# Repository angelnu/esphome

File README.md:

# esphome
This repository contains my devices based on [ESPHome](https://esphome.io/). Each yaml in this repository represents one of my devices and can be programed following the instructions bellow.

The [devices](devices) folder contains the instructions for each device (firmware, schematics, 3D boxes, etc).

## Programming
To program/update these devices you need to:
1. create a `secrets.yaml` file. You can use `secrets_template.yaml` as base
2. start the [esphome dashboard](https://esphome.io/guides/getting_started_command_line.html#bonus-esphome-dashboard) with this git repository as config folder.
3. Connect to the dashboard 
4. First time you program your device you will need to program via a serial port. You might use a [CP2104](https://www.amazon.de/gp/product/B01CYBHM26/ref=ppx_yo_dt_b_search_asin_title?ie=UTF8&psc=1)

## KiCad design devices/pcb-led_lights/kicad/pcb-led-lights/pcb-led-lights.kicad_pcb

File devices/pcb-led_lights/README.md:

# USB Power controller

This PCB allows controlling 7 LED strip channels up to 24V and 10A per channel. I use it to control a 5x channel RGBCWWW color led strip and a 2x channel CWWW white led strip with the same device. It uses a ESP32-C6 for the improved Wifi and Bluetooth as they are placed typically in locations with bad coverage such as celings and inside walls. I programmed a custom ESPHome component for the Motor Controlled PWM as the C6 and other ESP32 variants do not include enough LEDC channels.

It also includes a push button input so it can be used (limitedly) without connection if needed. If can also be used as Bluetooth proxy (at its Flash memory size). I intend to extend it later on to use Bluetooth Low Energy switches from Shelly so that it does not depend on the Home Assistant automation being available.

I ordered [20x already assembled PCBs from PCBWay](https://www.pcbway.com/project/shareproject/Strip_LED_Controller_for_ESPHome_e175d1c1.html) as I did not want to solder and check so many myself and I installed the whole house with these. PCBWay was kind to sponsor this PCB so here is the resulting project I ordered:

I received within a month for ca 16$ each of the 20x board with most of the cost for the components. The PCBs came wrapped individually (right in the picture above) and then in groups of five (pink wrap left in the picture). It took me a couple of hours to put it in the 3D printed box (which I printed myself but can be ordered from PCBWay as well) and upload the firmware via USB C cable (no serial adapter needed).

The LED from the ESP32 will light green when connecting to Wifi and blue after the connection has been stablished.

I have also [developed an adapter PCB to connect Ikea wardrobe LEDs with the TRÅDFRI system](https://www.printables.com/model/1427264-conector-for-ikea-tradfri).

[Aisler PCB project](https://aisler.net/p/KIGTGSCT) - Alternative PCBs - not tried assembly.

<details>
<summary>KiCad PCB - schematics and assembly </summary>

- [KiCad PCB project](KiCad/pcb-led-lights/pcb-led-lights.kicad_pro)
- 
- 
- 
- 
- 
- 
  
</details>

<details>
<summary>3D Printed Box </summary>

- [3D Printed box](FreeCAD)
- [FreeCad file](FreeCAD/pcb-led-lights.FCStd)
  - fix PCB with 3x M2 screws up to 7mm long (M2X6mm work great)
  - cover slack: 0.15 mm (enough that it holds without screws)
  - all parameters of the box are in the Settings Spreadsheet that you can change with FreeCAD if you need to adjust to your case
- [3MF file - small box](FreeCAD/pcb-led-lights-Box.3mf)

</details>

<details>
<summary>Parts</summary>

- 1x [ESP32-C6 Zero](https://www.waveshare.com/wiki/ESP32-C6-Zero) - this allows for wifi 6 and reduced components to solder as programer, led and antenna are included
- 1x [AP63203WU-7 Step-Down converter](https://www.mouser.com/datasheet/2/115/DIOD_S_A0007089856_1-2542907.pdf)
- 12x [Screw Terminal blocks](https://www.amazon.de/YIXISI-Terminal-Schraubklemme-Steckverbinder-Arduino/dp/B087RN8FDZ)
- 1x [2,9 uH inductor](https://www.mouser.com/datasheet/2/3/ASPI_0628-1775153.pdf)
- 7x [SUD40N06-25L Power MOSFET](https://www.farnell.com/datasheets/69243.pdf). Can also use [STD35NF06LT4](https://www.st.com/resource/en/datasheet/std35nf06l.pdf)
- 7x 0805 SMD 47 KOhms resistor
- 2x 0805 SMD 100 nF capacitor
- 2x 0805 SMD 22 uF capacitor
- 1x 0805 SMD 10 uF capacitor
  
</details>

<details>
<summary>Firmware</summary>

- You need to modify/create your own [ESPHome.io](https://esphome.io) definition and include the [yaml in this folder](rgbww_ww_v2.yaml)
- [Example for v2](TBD)

</details>

## ToDos

- [x] v2

## Changelog

### v2

- Complete redesign using an ESP32-C6 for better WiFi and step down to handle 24V (linear regulator was getting to hot in v1)

### v1

- First version

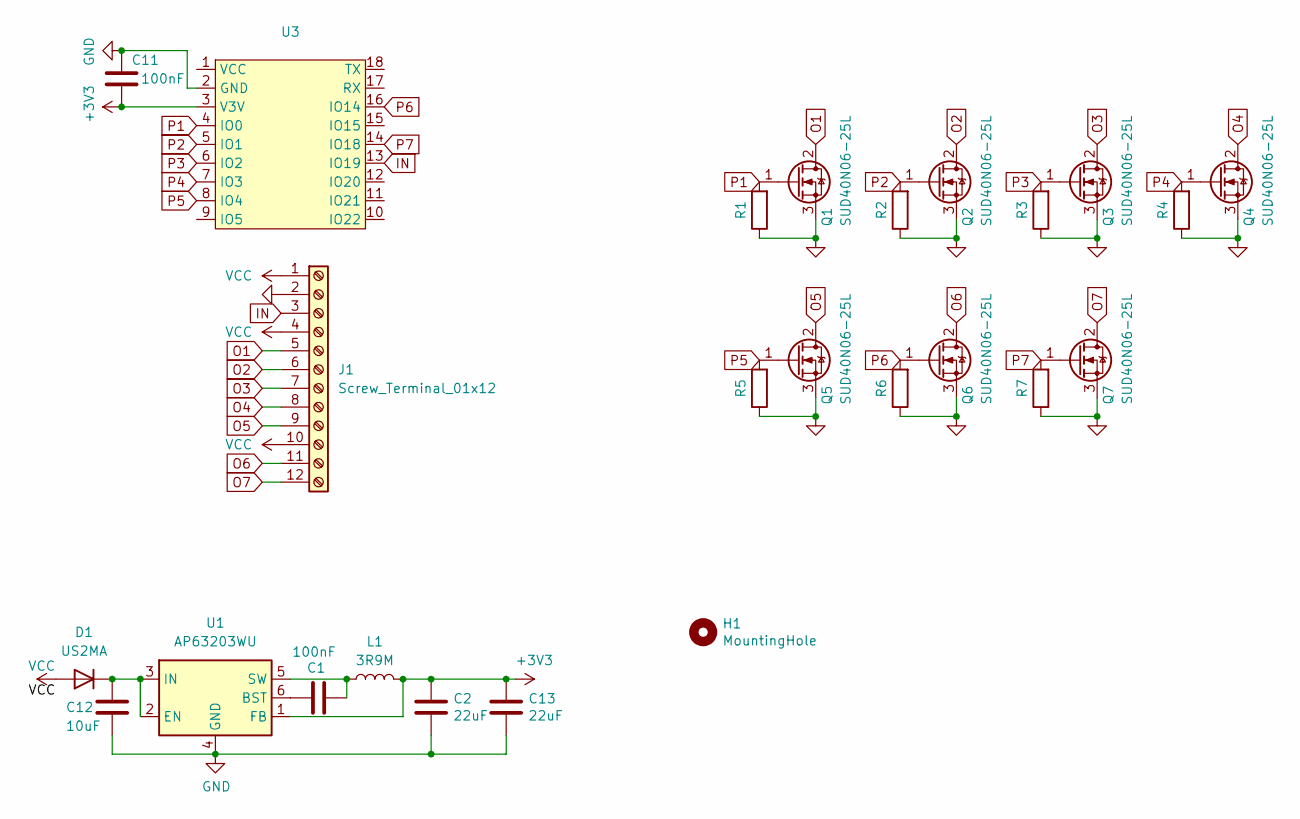
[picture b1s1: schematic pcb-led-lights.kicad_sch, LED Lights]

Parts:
C1, C11: 100nF; C_0805_2012Metric
C2, C13: 22uF; C_0805_2012Metric
C12: 10uF; C_0805_2012Metric
D1: US2MA; D_SMA
H1: MountingHole; MountingHole_2.2mm_M2
J1: Screw_Terminal_01x12; TerminalBlock_Phoenix_PT-1,5-12-5.0-H_1x12_P5.00mm_Horizont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
L1: 3R9M; L_APV_ANR6028
Q1, Q2, Q3, Q4, Q5, Q6, Q7: SUD40N06-25L; TO-252-2
R1, R2, R3, R4, R5, R6, R7: 12K; R_0805_2012Metric
U1: AP63203WU; TSOT-23-6
U3: Waveshare-ESP32-C6-Zero

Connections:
+3V3: C2.2, C11.1, C13.2, L1.2, U1.1 (FB), U3.3 (V3V)
GND: C2.1, C11.2, C12.1, C13.1, J1.2, Q1.3 (S), Q2.3 (S), Q3.3 (S), Q4.3 (S), Q5.3 (S), Q6.3 (S), Q7.3 (S), R1.1, R2.1, R3.1, R4.1, R5.1, R6.1, R7.1, U1.4 (GND), U3.2 (GND)
IN: J1.3, U3.13 (IO19)
unnamed: C12.2, D1.1 (K), U1.2 (EN), U1.3 (IN)
unnamed: C1.2, U1.6 (BST)
unnamed: C1.1, L1.1, U1.5 (SW)
O1: J1.5, Q1.2 (D)
O2: J1.6, Q2.2 (D)
O3: J1.7, Q3.2 (D)
O4: J1.8, Q4.2 (D)
O5: J1.9, Q5.2 (D)
O6: J1.11, Q6.2 (D)
O7: J1.12, Q7.2 (D)
P1: Q1.1 (G), R1.2, U3.4 (IO0)
P2: Q2.1 (G), R2.2, U3.5 (IO1)
P3: Q3.1 (G), R3.2, U3.6 (IO2)
P4: Q4.1 (G), R4.2, U3.7 (IO3)
P5: Q5.1 (G), R5.2, U3.8 (IO4)
P6: Q6.1 (G), R6.2, U3.16 (IO14)
P7: Q7.1 (G), R7.2, U3.14 (IO18)
VCC: D1.2 (A), J1.1, J1.4, J1.10

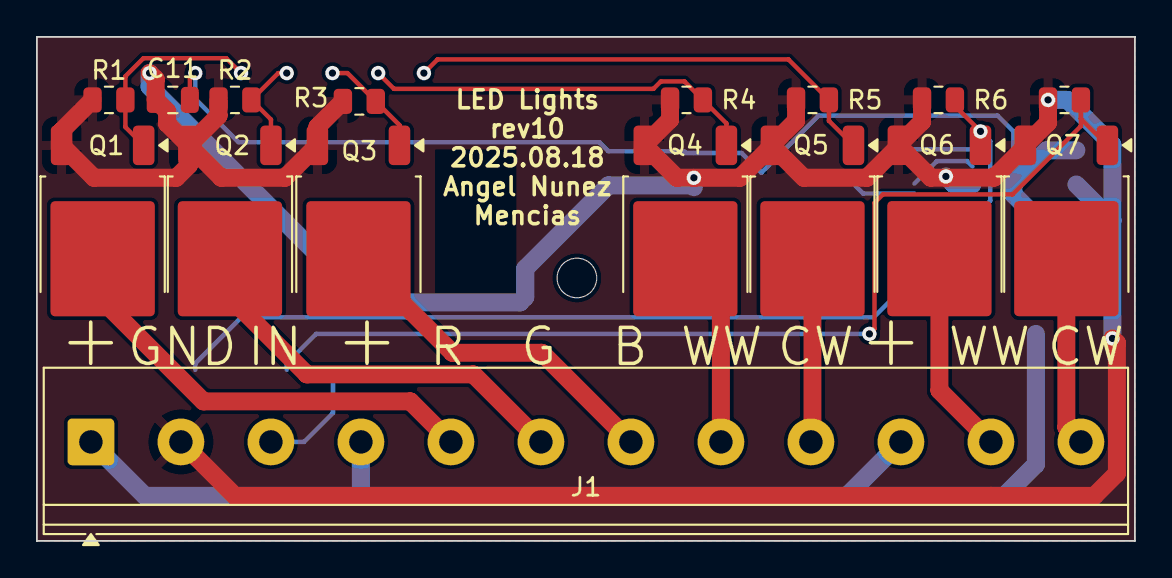
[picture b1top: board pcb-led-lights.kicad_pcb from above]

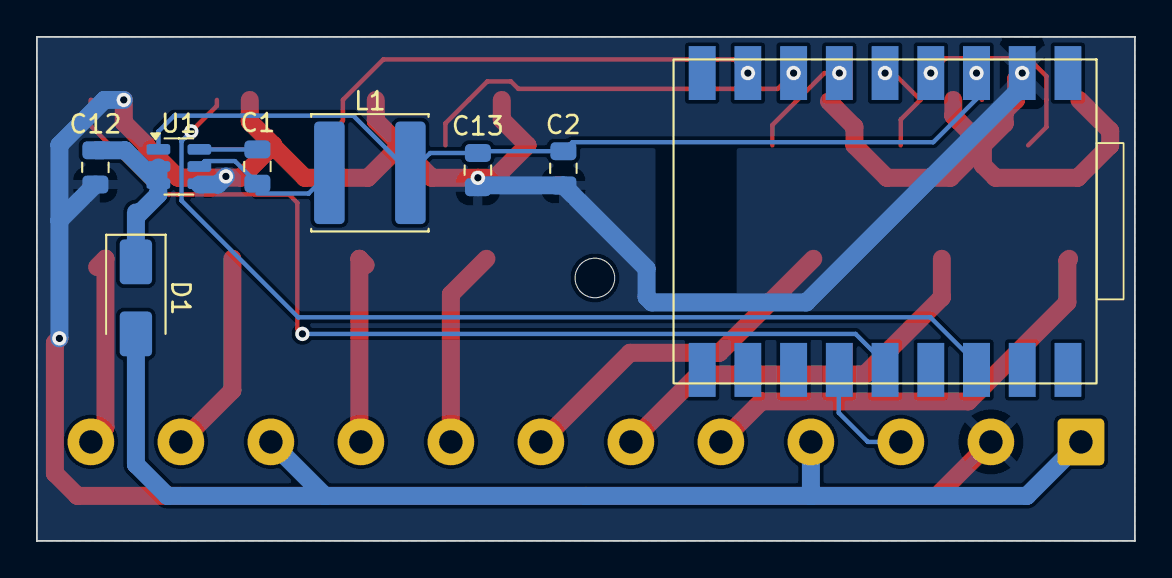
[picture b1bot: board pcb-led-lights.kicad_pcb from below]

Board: 2 copper layers, 61.0 x 28.0 mm, 25 parts (8 on the bottom side), 21 nets.

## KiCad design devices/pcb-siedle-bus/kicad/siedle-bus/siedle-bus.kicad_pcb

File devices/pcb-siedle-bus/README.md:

# Siedle In-Home bus client

This PCB allows interacting with a Sidle In-Home bus and automatically trigger actions or connect it to home automation such as [Home Assistant](https://www.home-assistant.io/). It uses [ESPHome](https://esphome.io) as base firmware. The power comes from the bus so no additional power supply is needed.

[Aisler PCB project](https://aisler.net/p/WQLXACYH)

<details>
<summary>KiCad PCB - schematics and assembly </summary>

- [KiCad PCB project](kicad/siedle-bus/siedle-bus.kicad_pro)
- 
  - [Simulation of Girator](https://www.circuitlab.com/circuit/edpfjhg6bu9k/siedle-inbus-girator/)
- 
- 
- 
- 
- 
  
</details>

<details>
<summary>3D Printed Box </summary>

- [3D Printed box](FreeCAD)
- [FreeCad file](FreeCAD/siedle-bus.FCStd)
  - fix PCB with 3x M2 screws up to 7mm long
  - use up to 3x 3mm wide screws to fix to the wall
  - cover slack: 0.15 mm (enough that it holds without screws)
  - all parameters of the box are in the Settings Spreadsheet that you can change with FreeCAD if you need to
    adjust to your case
- [3MF file - small box](FreeCAD/siedle-bus-cage.3mf)
- [3MF file - large box with placement template](FreeCAD/siedle-bus-cage_large.3mf)

</details>

<details>
<summary>Parts</summary>

- 1x [U1 - ESP32-WROOM-32 with 8MB Flash](https://www.espressif.com/sites/default/files/documentation/esp32-wroom-32_datasheet_en.pdf) / [src](https://www.chipspulse.com/product/Espressif-Systems/ESP32-WROOM-328MB.html)
- 1x [U2 - Step-down Buck Power MP1584EN Modul](https://www.ebay.de/itm/375340664282) / [alt](https://www.domoticx.net/webshop/spanningsregelaar-module-dc-dc-step-down-5-28v-naar-33v-max-3a-mp1584en/)
- 1x [2 Pin Screw Terminal blocks](https://www.amazon.de/YIXISI-Terminal-Schraubklemme-Steckverbinder-Arduino/dp/B087RN8FDZ)
- 1x [C2 - 1F 5V Supercapacitor](https://www.ebay.de/itm/126559349843) / [alt](https://www.opencircuit.nl/product/1f-supercondensator-5.5v-1-stuk)
- 2x [C3 - 220uF Elec 8x10.5 mm capacitor](https://www.ebay.de/itm/175443736870) / [alt](https://www.amazon.de/dp/B0D7GXFJ55)
- 3x [Q1, Q4, Q5 - IRLML2402 MOSFET Transistor](https://www.ebay.de/itm/114510586115) / [alt](https://www.amazon.de/dp/B08M38TJM3)
- 2x [Q2, Q3 - BC807 PNP Bipolar Transistor](https://www.ebay.de/itm/284104594986?var=585596351672) / [alt](https://www.amazon.de/dp/B08M3NZTW4)
- 1x [program_port1 - 4 pin 2.54 mm Breakaway Board Connector Header](https://www.ebay.de/itm/272575130016) / [alt](https://www.amazon.de/dp/B09BDX69VX)
- 1x [R10 - 0805 SMD 12 KOhms resistor (it can be 10K as well)](https://www.ebay.de/itm/305754891633) / [alt](https://www.amazon.de/dp/B07DK3322P)
- 5x [R1, R5, R6, 15, R16 - 0805 SMD 10 KOhms resistor](https://www.ebay.de/itm/305754891633) / [alt](https://www.amazon.de/dp/B07DK3322P)
- 1x [R7 - 0805 SMD 2 KOhms resistor](https://www.ebay.de/itm/305754891633) / [alt](https://www.amazon.de/dp/B07DK3322P)
- 2x [R8, R9 - 0805 SMD 1 KOhms resistor](https://www.ebay.de/itm/305754891633) / [alt](https://www.amazon.de/dp/B07DK3322P)
- 1x [R11 - 0805 SMD 200 Ohms resistor](https://www.ebay.de/itm/305754891633) / [alt](https://www.amazon.de/dp/B07DK3322P)
- 1x [R3 - 0805 SMD 120 Ohms resistor](https://www.ebay.de/itm/305754891633) / [alt](https://www.amazon.de/dp/B07DK3322P)
- 2x [R2, R4 - 0805 SMD 47 Ohms resistor](https://www.ebay.de/itm/305754891633) / [alt](https://www.amazon.de/dp/B07DK3322P)
- 1x [R12 - 0805 SMD 10 Ohms resistor](https://www.ebay.de/itm/305754891633) / [alt](https://www.amazon.de/dp/B07DK3322P)
- 2x [R13, R14 - 0805 SMD 0 Ohms resistor](https://www.ebay.de/itm/305754891633) / [alt](https://www.amazon.de/dp/B07DK3322P)
- 2x [C1, C11 - 0805 SMD 100 nF capacitor](https://www.ebay.de/itm/176105462805) / [alt](https://www.amazon.de/dp/B07DK4CM4W)
- 2x [D1, D2 - BYG21M 1000V 1.5A DO214AC diode](https://www.amazon.de/dp/B0DGGWWMLS)
  
</details>

<details>
<summary>Pins</summary>

- Bus connector (ETR not used). From top to bottom:
  - Tb-
  - Ta+
- Serial programming:
  - 3.3V
  - TX
  - RX
  - GND

</details>

<details>
<summary>Firmware</summary>

- You need to modify/create your own [ESPHome.io](https://esphome.io) definition and include the [yaml in this folder](v1.yaml)
- [Example for v1.0](../../interphone_small_flat.yaml)

</details>

## Bus information

The bus uses only 2 wires for communication and powering devices. A third wire is also present but not used here.

The bus provides 27V and can power client devices for up to 15mA (in the original board circuit there is a current limiter). It is very important to ensure that a high impedance is present to AC to not affect the bus communication. This is achieved in this project using a [Girator](https://en.wikipedia.org/wiki/Gyrator). The girator in this project uses a MOSFET to implement the girator and implement a virtual coil.

To prepare the bus to send a message, the bus is first shorted with 200 Ohms. This triggers the power supply of the bus to lower the current and allow the bits of the message to be sent. To send the bits a resistor of 10 ohms in parallel to the 200 Ohms is used to signal a zero while the 200 Ohms signal a 1. Each bit is 2 ms.

The PCB in this project uses a PNP Bipolar transistor to detect the bus carrier (when the voltage is dropped) and the following message bits. An NPN MOSFET is used to add the resistors to the bus.

### Message

Each message sent in the bus has 32 bits:

- 31-29: 010
- 28-23: command
- 22-18: destination
- 17-14: destination bus
- 13-12: 010 (first bit might be 1)
- 10-06: source
- 05-02: source bus
- 01-00: 00 (first bit might be 1 - broadcast?)

### References

I used all the reverse engineering from this [mikrocontroller Forum thread (german)](https://www.mikrocontroller.net/topic/308271) as base. Thanks a lot for all that contributed there.

Example of devices using this bus:

- [aib-150-01 Vendor page](https://www.siedle.de/de-de/home/service/linked-pages/produktkatalog/tuersprechanlagen-innen/siedle-basic/aib-150-01/)

### ToDos

- [x] switch to esp-idf framework

## Changelog

### v1

- First version

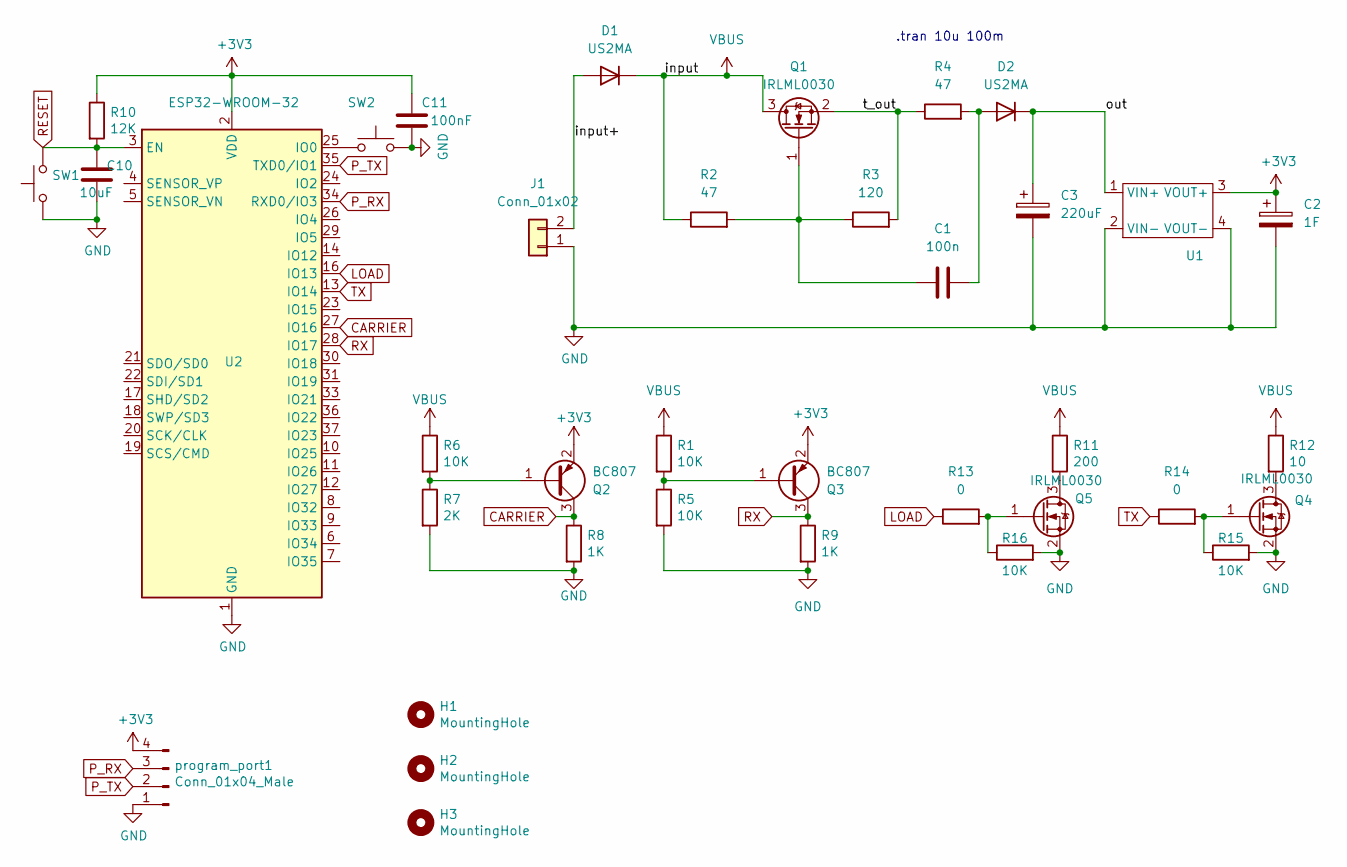
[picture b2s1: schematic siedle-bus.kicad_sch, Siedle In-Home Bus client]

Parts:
C1: 100n; C_0805_2012Metric
C2: 1F; CP_Radial_Tantal_D20.5mm_P5.00mm
C3: 220uF; CP_Elec_8x10.5
C10: 10uF; C_0805_2012Metric
C11: 100nF; C_0805_2012Metric
D1, D2: US2MA; D_SMA
H1, H2, H3: MountingHole; MountingHole_2.2mm_M2
J1: Conn_01x02; PhoenixContact_MCV_1,5_2-G-5.08_1x02_P5.08mm_Vertical
Q1, Q4, Q5: IRLML0030; SOT-23
Q2, Q3: BC807; SOT-23
R1, R5, R6, R15, R16: 10K; R_0805_2012Metric
R2, R4: 47; R_0805_2012Metric
R3: 120; R_0805_2012Metric
R7: 2K; R_0805_2012Metric
R8, R9: 1K; R_0805_2012Metric
R10: 12K; R_0805_2012Metric
R11: 200; R_0805_2012Metric
R12: 10; R_0805_2012Metric
R13, R14: 0; R_0805_2012Metric
SW1: RESET; SW_SPST_PTS810
SW2: BOOT; SW_SPST_PTS810
U1: SRT_MPT1584EN_Module
U2: ESP32-WROOM-32
program_port1: Conn_01x04_Male; PinHeader_1x04_P2.54mm_Vertical

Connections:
+3V3: C2.1, C11.2, Q2.2 (E), Q3.2 (E), R10.1, U1.3 (VOUT+), U2.2 (VDD), program_port1.4
/input+: D1.2 (A), J1.2
/out: C3.1, D2.1 (K), U1.1 (VIN+)
/t_out: Q1.2 (S), R3.2, R4.1
CARRIER: Q2.3 (C), R8.1, U2.27 (IO16)
GND: C2.2, C3.2, C10.1, C11.1, J1.1, Q4.2 (S), Q5.2 (S), R5.2, R7.2, R8.2, R9.2, R15.2, R16.2, SW1.1, SW2.2, U1.2 (VIN-), U1.4 (VOUT-), U2.1 (GND), U2.15 (GND), U2.38 (GND), U2.39 (GND), program_port1.1
LOAD: R13.1, U2.16 (IO13)
unnamed: C1.2, D2.2 (A), R4.2
unnamed: C1.1, Q1.1 (G), R2.2, R3.1
unnamed: Q2.1 (B), R6.2, R7.1
unnamed: Q3.1 (B), R1.2, R5.1
unnamed: Q4.3 (D), R12.2
unnamed: Q4.1 (G), R14.2, R15.1
unnamed: Q5.3 (D), R11.2
unnamed: Q5.1 (G), R13.2, R16.1
unnamed: SW2.1, U2.25 (IO0)
P_RX: U2.34 (RXD0/IO3), program_port1.3
P_TX: U2.35 (TXD0/IO1), program_port1.2
RESET: C10.2, R10.2, SW1.2, U2.3 (EN)
RX: Q3.3 (C), R9.1, U2.28 (IO17)
TX: R14.1, U2.13 (IO14)
VBUS: D1.1 (K), Q1.3 (D), R1.1, R2.1, R6.1, R11.1, R12.1

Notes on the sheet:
.tran 10u 100m

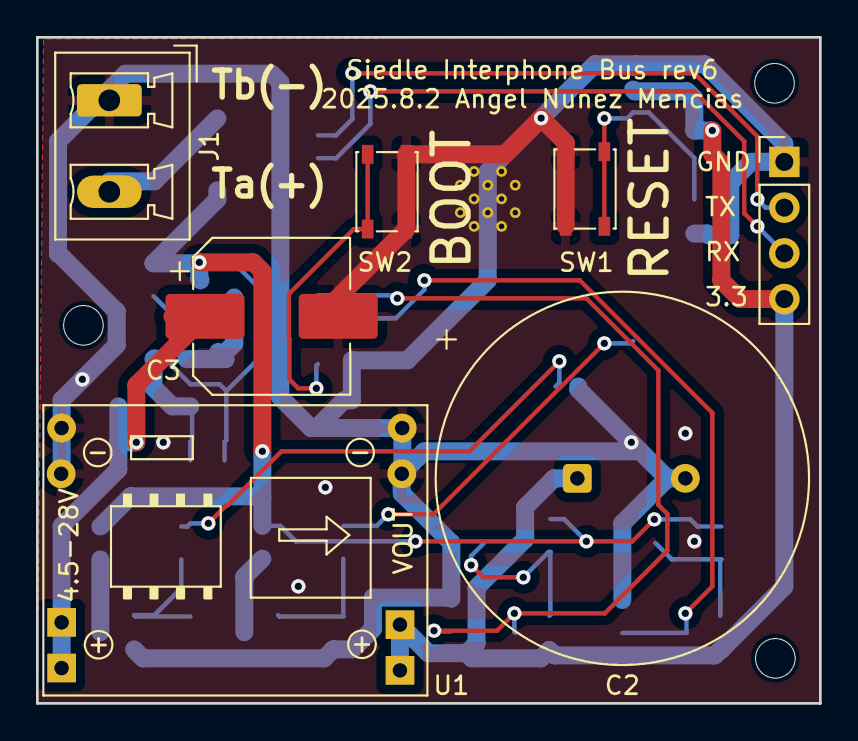
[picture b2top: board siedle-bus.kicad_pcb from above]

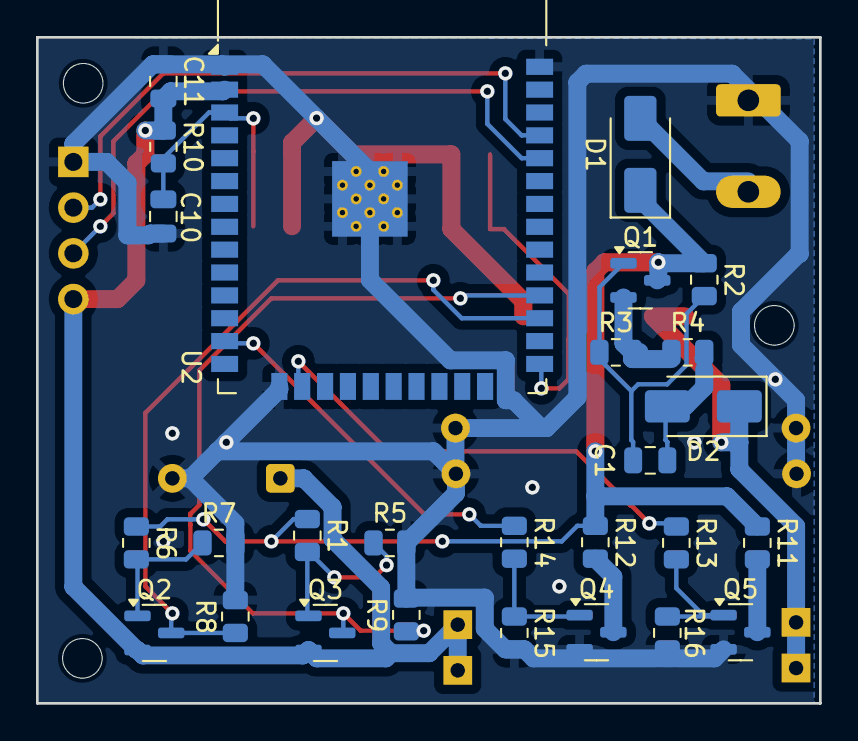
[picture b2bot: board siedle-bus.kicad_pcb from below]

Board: 2 copper layers, 43.5 x 37.0 mm, 37 parts (27 on the bottom side), 22 nets.

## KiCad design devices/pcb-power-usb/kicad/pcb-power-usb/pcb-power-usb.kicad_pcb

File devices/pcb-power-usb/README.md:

# USB Power controller

This PCB allows providing 5 V for up to 8 USB devices. Each of them can be disabled via esphome. Each USB has an LED to indicate if power is provided.

- 

- [Aisler PCB project](https://aisler.net/p/BQLUSDIS)
- [KiCad PCB](kicad/pcb-power-usb/pcb-power-usb.kicad_pro)
  - 
  - 
  - 
- [3D Printed cage](cage):
  - [Fusion 360 online view](https://a360.co/3qWptNk)
  - [Fusion 360 archive](cage/pcb-power-usb.f3z)

- Parts:
  - 1x [ESP32-WROOM-32](https://www.espressif.com/sites/default/files/documentation/esp32-wroom-32_datasheet_en.pdf)
  - 1x [AMS1117 - 3,3v 1A regulator in SOT-223 format](http://www.advanced-monolithic.com/pdf/ds1117.pdf)
  - 8x [IRLML0030 - 5A N-MOSFET](https://www.infineon.com/dgdl/Infineon-IRLML0030-DataSheet-v01_01-EN.pdf?fileId=5546d462533600a401535664773825df)
  - 8x [USB_A_Stewart_SS-52100-001_Horizontal](https://www.digikey.de/en/products/detail/stewart-connector/SS-52100-001/7902377)
  - 8x 0805 LEDs
  - 8x 0805 LED resistors (depends on selected LED)
  - 1x 10 KOhm resistor (reset)
  - 9x 0805 10 uF capacitor
  - 1x DC 5.5 x 2.1 mm barrel connector
    - Bought from [Amazon](https://www.amazon.de/gp/product/B093FTFZ8Q)
- PINs:
  - Header top left - external temperature sensors. From top to bottom:
    - VCC
    - Data
    - GND
- Firmware: [esphome](esphome.io)
  - You need to modify/create your own esphome definition and include the yaml in this folder matching your PCB
  - [Example for v1.0](../../s13-legos-shelves.yaml)

# Changelog

## v1.0
  - First version
  - BUGS:
    - None so far

## v2.0
    - use outputs instead of switches so optionally lights can be used

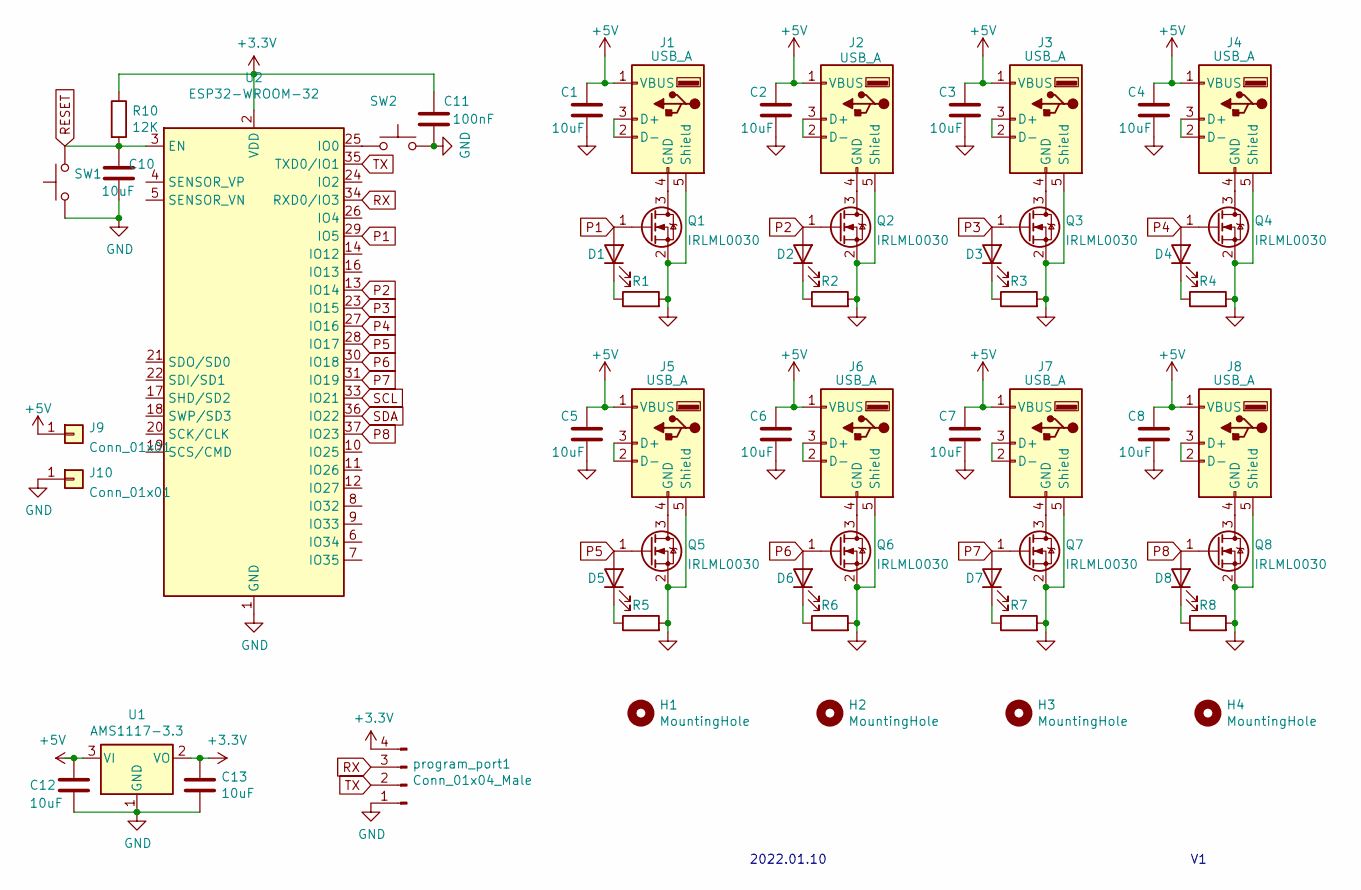
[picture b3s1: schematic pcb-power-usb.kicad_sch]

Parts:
C1, C2, C3, C4, C5, C6, C7, C8, C10, C12, C13: 10uF; C_0805_2012Metric
C11: 100nF; C_0805_2012Metric
D1, D2, D3, D4, D5, D6, D7, D8: LED; LED_0805_2012Metric_Pad1.15x1.40mm_HandSolder
H1, H2, H3, H4: MountingHole; MountingHole_2.2mm_M2
J1, J2, J3, J4, J5, J6, J7, J8: USB_A; USB_A_Stewart_SS-52100-001_Horizontal
J9, J10: Conn_01x01; SolderWire-1sqmm_1x01_D1.4mm_OD2.7mm
Q1, Q2, Q3, Q4, Q5, Q6, Q7, Q8: IRLML0030; SOT-23
R1, R2, R3, R4, R5, R6, R7, R8: R; R_0805_2012Metric
R10: 12K; R_0805_2012Metric
SW1, SW2: SW_Push; SW_SPST_PTS810
U1: AMS1117-3.3; SOT-223-3_TabPin2
U2: ESP32-WROOM-32
program_port1: Conn_01x04_Male; PinHeader_1x04_P2.54mm_Vertical

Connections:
+3V3: C11.2, C13.2, R10.1, U1.2 (VO), U2.2 (VDD), program_port1.4
+5V: C1.2, C2.2, C3.2, C4.2, C5.2, C6.2, C7.2, C8.2, C12.2, J1.1 (VBUS), J2.1 (VBUS), J3.1 (VBUS), J4.1 (VBUS), J5.1 (VBUS), J6.1 (VBUS), J7.1 (VBUS), J8.1 (VBUS), J9.1, U1.3 (VI)
GND: C1.1, C2.1, C3.1, C4.1, C5.1, C6.1, C7.1, C8.1, C10.1, C11.1, C12.1, C13.1, J1.5 (Shield), J2.5 (Shield), J3.5 (Shield), J4.5 (Shield), J5.5 (Shield), J6.5 (Shield), J7.5 (Shield), J8.5 (Shield), J10.1, Q1.2 (S), Q2.2 (S), Q3.2 (S), Q4.2 (S), Q5.2 (S), Q6.2 (S), Q7.2 (S), Q8.2 (S), R1.2, R2.2, R3.2, R4.2, R5.2, R6.2, R7.2, R8.2, SW1.1, SW2.2, U1.1 (GND), U2.1 (GND), U2.15 (GND), U2.38 (GND), U2.39 (GND), program_port1.1
unnamed: D1.1 (K), R1.1
unnamed: D2.1 (K), R2.1
unnamed: D3.1 (K), R3.1
unnamed: D4.1 (K), R4.1
unnamed: D5.1 (K), R5.1
unnamed: D6.1 (K), R6.1
unnamed: D7.1 (K), R7.1
unnamed: D8.1 (K), R8.1
unnamed: J1.2 (D-), J1.3 (D+)
unnamed: J1.4 (GND), Q1.3 (D)
unnamed: J2.2 (D-), J2.3 (D+)
unnamed: J2.4 (GND), Q2.3 (D)
unnamed: J3.2 (D-), J3.3 (D+)
unnamed: J3.4 (GND), Q3.3 (D)
unnamed: J4.2 (D-), J4.3 (D+)
unnamed: J4.4 (GND), Q4.3 (D)
unnamed: J5.2 (D-), J5.3 (D+)
unnamed: J5.4 (GND), Q5.3 (D)
unnamed: J6.2 (D-), J6.3 (D+)
unnamed: J6.4 (GND), Q6.3 (D)
unnamed: J7.2 (D-), J7.3 (D+)
unnamed: J7.4 (GND), Q7.3 (D)
unnamed: J8.2 (D-), J8.3 (D+)
unnamed: J8.4 (GND), Q8.3 (D)
unnamed: SW2.1, U2.25 (IO0)
P1: D1.2 (A), Q1.1 (G), U2.29 (IO5)
P2: D2.2 (A), Q2.1 (G), U2.13 (IO14)
P3: D3.2 (A), Q3.1 (G), U2.23 (IO15)
P4: D4.2 (A), Q4.1 (G), U2.27 (IO16)
P5: D5.2 (A), Q5.1 (G), U2.28 (IO17)
P6: D6.2 (A), Q6.1 (G), U2.30 (IO18)
P7: D7.2 (A), Q7.1 (G), U2.31 (IO19)
P8: D8.2 (A), Q8.1 (G), U2.37 (IO23)
RESET: C10.2, R10.2, SW1.2, U2.3 (EN)
RX: U2.34 (RXD0/IO3), program_port1.3
SCL: U2.33 (IO21)
SDA: U2.36 (IO22)
TX: U2.35 (TXD0/IO1), program_port1.2

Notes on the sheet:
2022.01.10

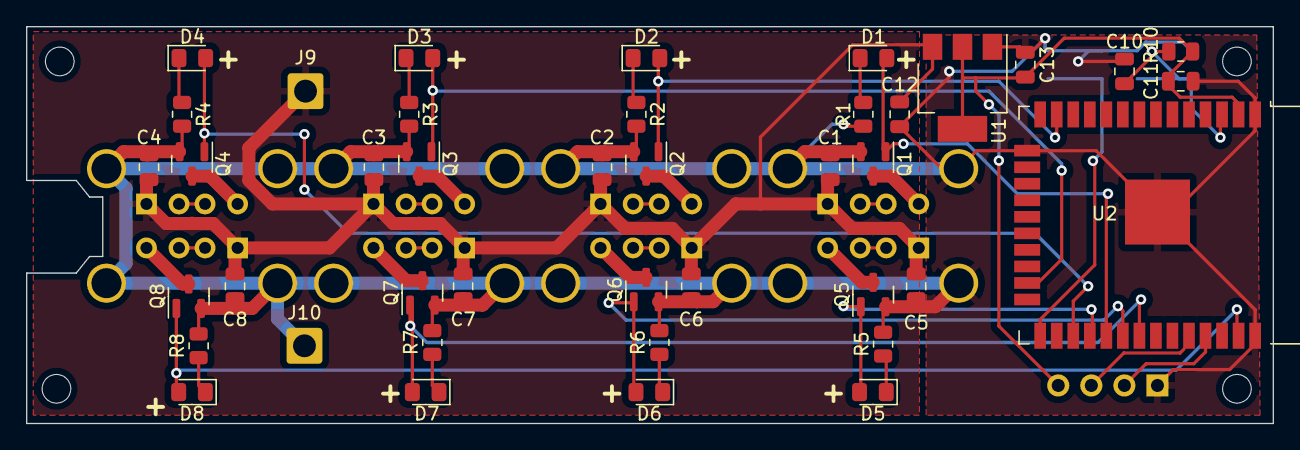
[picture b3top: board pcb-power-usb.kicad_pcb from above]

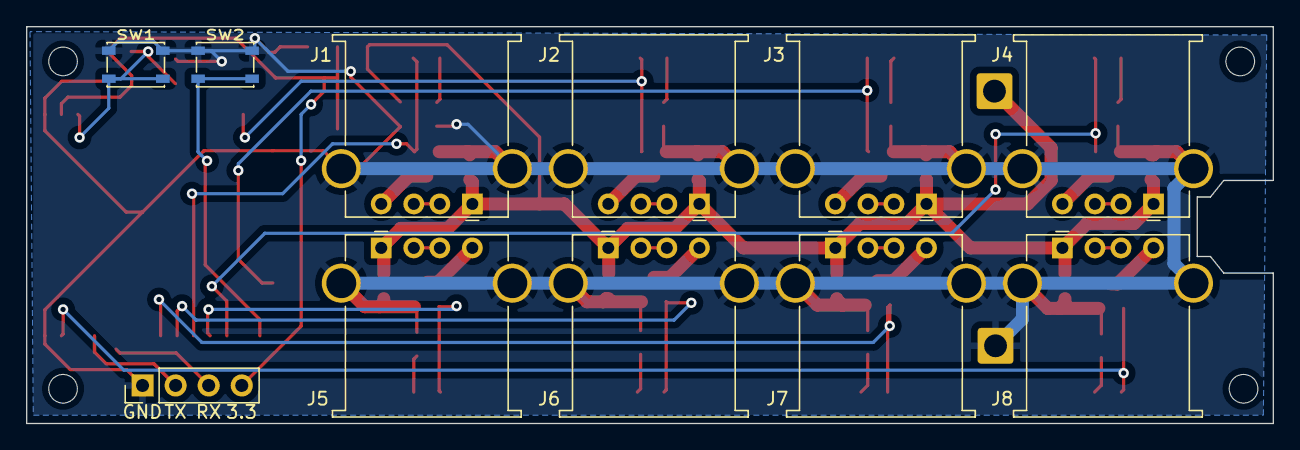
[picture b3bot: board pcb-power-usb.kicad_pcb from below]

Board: 2 copper layers, 95.8 x 30.5 mm, 56 parts (11 on the bottom side), 39 nets.

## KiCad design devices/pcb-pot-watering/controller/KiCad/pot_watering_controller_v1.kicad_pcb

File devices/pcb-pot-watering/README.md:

# Pot watering
This PCB allows watering pots with individual sensor and pumpes. The main feature is that the settings are stored in the sensor so you can disconned a pot from the controller and move with its sensor to another contoller: the watering settings will be transported.

TBD: more explanations

## Controller

- [Aisler PCB project](https://aisler.net/p/DESISEWY)
- [KiCad schematics](controller/KiCad/pot_watering_controller_v1.sch)
  - 
- [KiCad PCB](controller/KiCad/pot_watering_controller_v1.kicad_pcb)
  - 
  - 
- Parts:
  - 1x [ESP32-WROOM-32](https://www.espressif.com/sites/default/files/documentation/esp32-wroom-32_datasheet_en.pdf)
  - 2x pression sensors [LPS33HWTR](https://www.st.com/resource/en/datasheet/lps33hw.pdf)
  - 1x accelerometer [LIS3DH](https://www.st.com/resource/en/datasheet/cd00274221.pdf)
  - 1x IC power switch [MCZ33996EK](https://www.nxp.com/docs/en/data-sheet/MC33996.pdf)
  - 6 or 10 [RJ-45 Modular Jack - 98435-111LF](https://www.amphenol-icc.com/modular-jack-98435111lf.html)
  - 6 or 10 connectors
- PINs:
  - Serial programmer:
    1. VCC
    2. RX
    3. TX
    4. GND
 - Power
 - 6 or 10 pumpe power ports
 - 6 or 10 ethernet ports
- Firmwares:
  - [esphome](esphome.io)
    - You need to modify/create your own esphome definition and include the yaml in this folder matching your PCB
    - [Example for v1.1](../../w1-test.yaml)
  - [platformio](platformio.io) For testing without esphome you can use platformio to build and standalone test firmware that will periodically refresh the sensor data and print it to serial
    1. install [platformio](platformio.io)
    2. open a terminal at the [controller folder](controller)
    3. connect your ep32 via serial to your computer
    4. ensure your serial adapter matches the monitoring and programming sections in the [platformio config file](controller/platformio.ini).
    5. run `pio upload`

### Changelog

#### v1.1
  - First version
  - BUGS:
    - TBD

## Sensor
- [Aisler PCB project](https://aisler.net/p/HRCGITXS)
- [KiCad schematics](sensor/KiCad/SoilSensor_spi.sch)
  - 
- [KiCad PCB](sensor/KiCad/SoilSensor_spi.kicad_pcb)
  - 
  - 
  - 
- Parts:
  - TBD
- PINs:
  - TBD
- Firmware: [platformio](platformio.io)
  1. install [platformio](platformio.io)
  1. open a terminal at the [sensor folder](sensor)
  2. connect your sensor board via [STLink](https://www.st.com/en/development-tools/st-link-v2.html) to your computer
  3. run `pio upload`
- [3D Printed cage](cages):
  - 
  - 

### Changelog

#### v1.1
  - First version
  - BUGS:
    - TBD

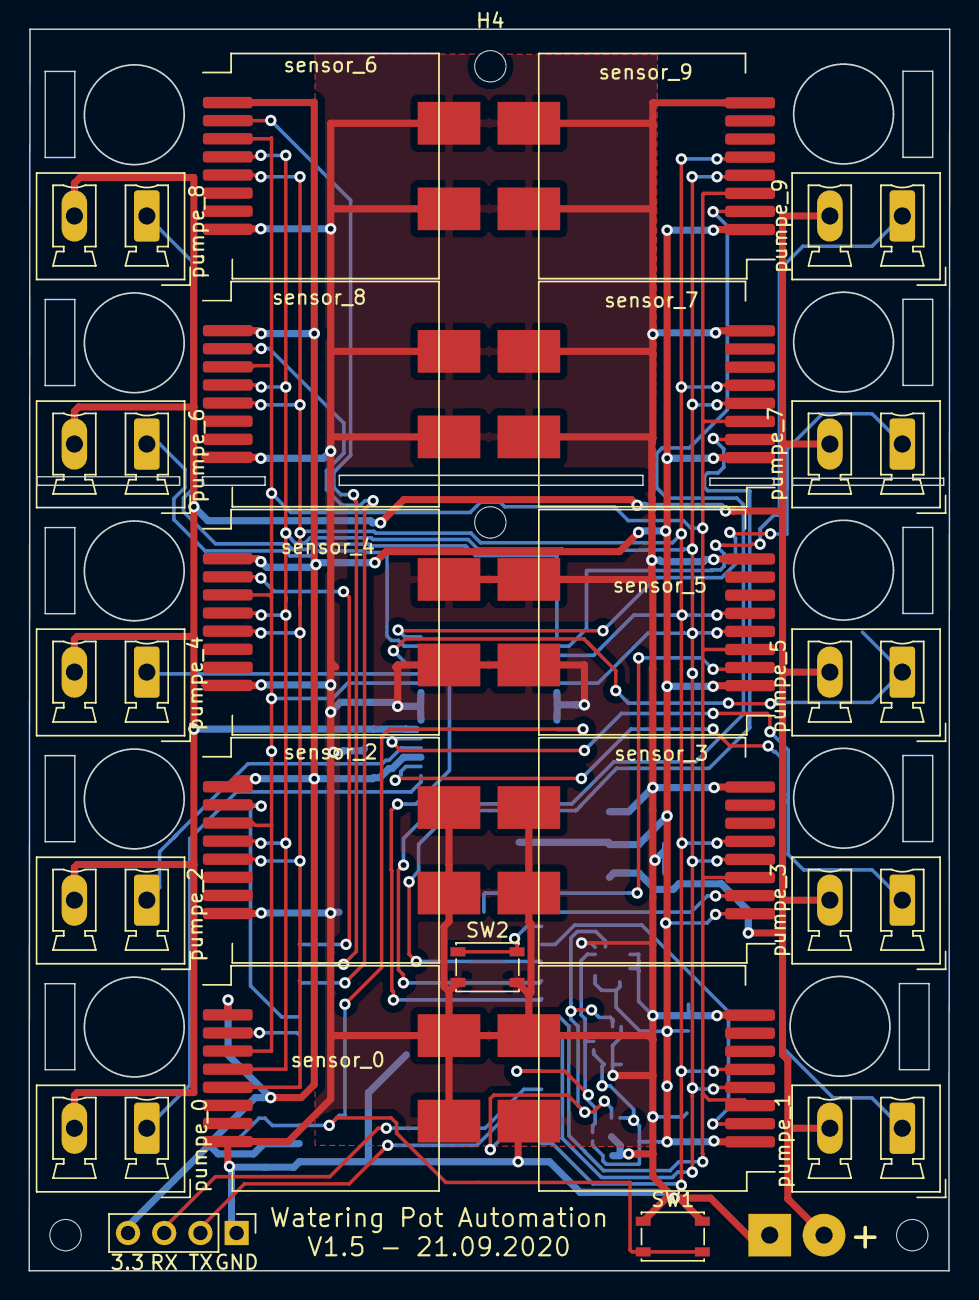
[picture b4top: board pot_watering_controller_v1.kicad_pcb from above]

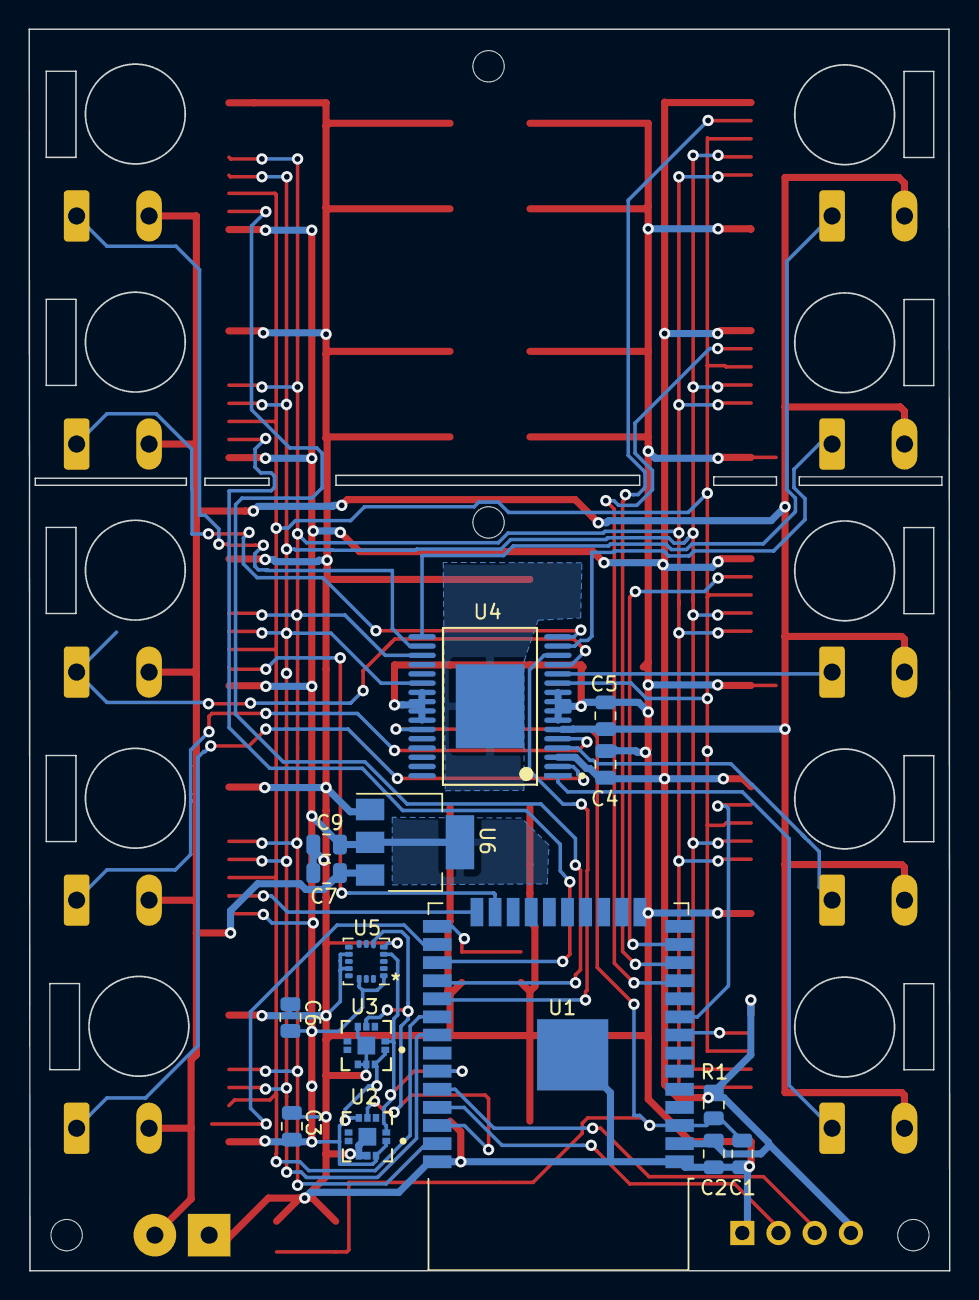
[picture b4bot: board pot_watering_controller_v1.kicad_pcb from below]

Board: 2 copper layers, 64.6 x 87.1 mm, 43 parts (15 on the bottom side), 33 nets.

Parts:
C1, C7, C9: 10uF; C_0805_2012Metric
C2, C3, C4, C5, C6: 100nF; C_0805_2012Metric
H1, H2, H3, H4: MountingHole; MountingHole_2.2mm_M2
Power1: Conn_01x02; SolderWirePad_1x02_P3.81mm_Drill1.2mm
R1: 12K; R_0805_2012Metric
SW1, SW2: SW_Push; SW_SPST_PTS810
U1: ESP32-WROOM-32
U2, U3: LPS33HWTR; STMicroelectronics-CCLGA-10L-DM00294349-0-2-MFG
U4: MCZ33996EK; NXP-MCZ33996EK-IPC_A
U5: LIS3DH; LGA-16_3x3mm_P0.5mm_LayoutBorder3x5y
U6: AMS1117-3.3; SOT-223-3_TabPin2
program_port1: Conn_01x04_Male; PinHeader_1x04_P2.54mm_Vertical
pumpe_0, pumpe_1, pumpe_2, pumpe_3, pumpe_4, pumpe_5, pumpe_6, pumpe_7, pumpe_8, pumpe_9: pumpe; PhoenixContact_MCV_1,5_2-G-5.08_1x02_P5.08mm_Vertical
sensor_0, sensor_1, sensor_2, sensor_3, sensor_4, sensor_5, sensor_6, sensor_7, sensor_8, sensor_9: RJ45; RJ45_fciconnector_vertical

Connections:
+3V3: C2.2, C3.2, C4.2, C6.1, C9.2, R1.1, U1.2, U2.1, U2.5, U2.10, U3.1, U3.10, U4.3, U5.1, U5.14, U6.2, program_port1.4, sensor_0.1, sensor_1.1, sensor_2.1, sensor_3.1, sensor_4.1, sensor_5.1, sensor_6.1, sensor_7.1, sensor_8.1, sensor_9.1
GND: C1.1, C2.1, C3.1, C4.1, C5.1, C6.2, C7.1, C9.1, Power1.1, SW1.1, SW2.2, U1.1, U1.15, U1.38, U1.39, U2.8, U2.9, U2.11, U3.5, U3.8, U3.9, U3.11, U4.7, U4.8, U4.9, U4.10, U4.23, U4.24, U4.25, U4.26, U5.5, U5.10, U5.12, U6.1, program_port1.1, sensor_0.8, sensor_0.SH, sensor_1.8, sensor_1.SH, sensor_2.8, sensor_2.SH, sensor_3.8, sensor_3.SH, sensor_4.8, sensor_4.SH, sensor_5.8, sensor_5.SH, sensor_6.8, sensor_6.SH, sensor_7.8, sensor_7.SH, sensor_8.8, sensor_8.SH, sensor_9.8, sensor_9.SH
MISO: U1.31, U4.22, sensor_0.4, sensor_1.4, sensor_2.4, sensor_3.4, sensor_4.4, sensor_5.4, sensor_6.4, sensor_7.4, sensor_8.4, sensor_9.4
MOSI: U1.37, U4.19, sensor_0.5, sensor_1.5, sensor_2.5, sensor_3.5, sensor_4.5, sensor_5.5, sensor_6.5, sensor_7.5, sensor_8.5, sensor_9.5
NS_pumpes: U1.29, U4.14
NS_sensor_00: U1.8, sensor_0.2
NS_sensor_01: U1.26, sensor_1.2
NS_sensor_02: U1.9, sensor_2.2
NS_sensor_03: U1.24, sensor_3.2
NS_sensor_04: U1.13, sensor_4.2
NS_sensor_05: U1.23, sensor_5.2
NS_sensor_06: U1.11, sensor_6.2
NS_sensor_07: U1.27, sensor_7.2
NS_sensor_08: U1.12, sensor_8.2
NS_sensor_09: U1.28, sensor_9.2
unnamed: SW2.1, U1.25
RESET: C1.2, R1.2, SW1.2, U1.3, U4.27
RX: U1.34, program_port1.3
SCL: U1.33, U2.2, U3.2, U5.4
SCLK: U1.30, U4.11, sensor_0.3, sensor_1.3, sensor_2.3, sensor_3.3, sensor_4.3, sensor_5.3, sensor_6.3, sensor_7.3, sensor_8.3, sensor_9.3
SDA: U1.36, U2.4, U3.4, U5.6
TX: U1.35, program_port1.2
VCC: C5.2, C7.2, Power1.2, U4.6, U6.3, pumpe_0.2, pumpe_1.2, pumpe_2.2, pumpe_3.2, pumpe_4.2, pumpe_5.2, pumpe_6.2, pumpe_7.2, pumpe_8.2, pumpe_9.2
pumpe_00: U4.1, pumpe_0.1
pumpe_01: U4.2, pumpe_1.1
pumpe_02: U4.4, pumpe_2.1
pumpe_03: U4.5, pumpe_3.1
pumpe_04: U4.12, pumpe_4.1
pumpe_05: U4.13, pumpe_5.1
pumpe_06: U4.15, pumpe_6.1
pumpe_07: U4.16, pumpe_7.1
pumpe_08: U4.17, pumpe_8.1
pumpe_09: U4.18, pumpe_9.1

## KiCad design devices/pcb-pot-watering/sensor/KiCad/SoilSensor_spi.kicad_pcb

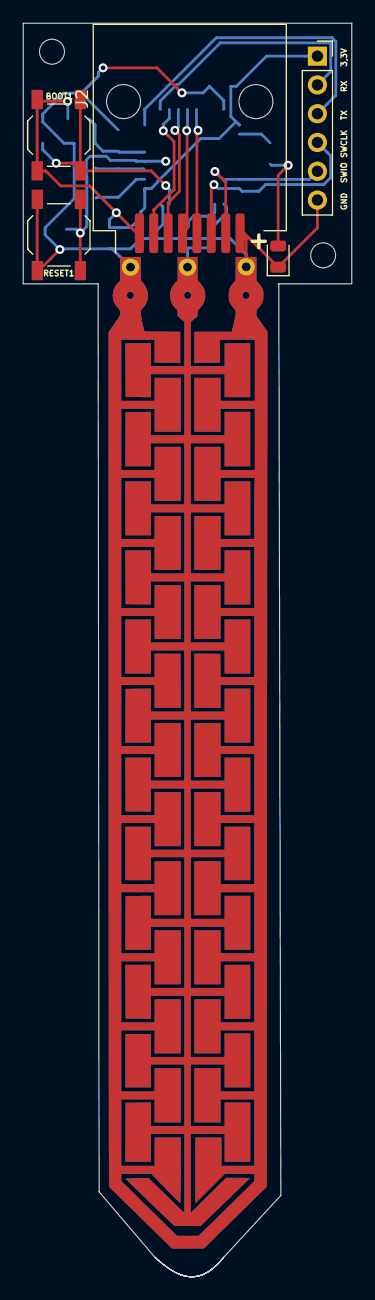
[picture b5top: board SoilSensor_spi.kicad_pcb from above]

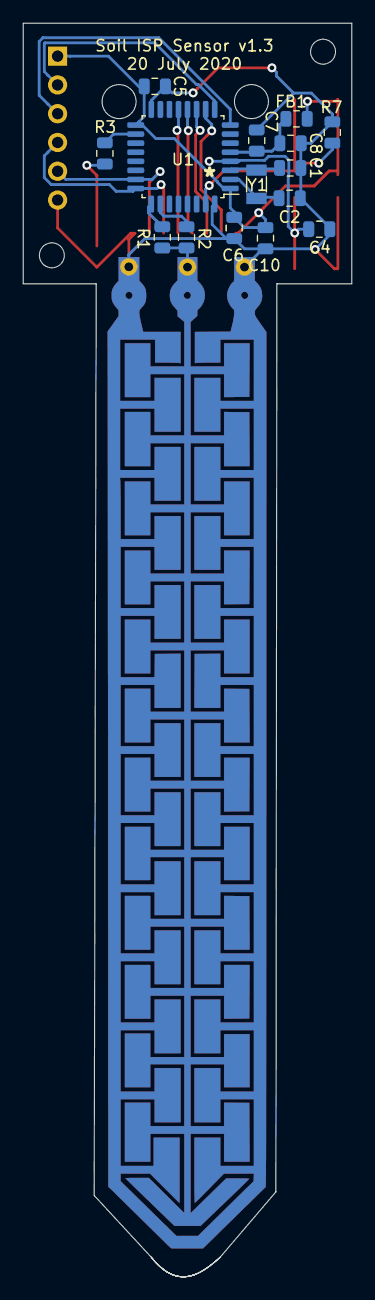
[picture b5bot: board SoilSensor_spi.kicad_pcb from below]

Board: 2 copper layers, 29.0 x 110.6 mm, 23 parts (15 on the bottom side), 20 nets.

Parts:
BOOT1: BOOT; SW_SPST_TL3342
C1, C2: 10 pF; C_0805_2012Metric
C4, C5, C6, C7: 100 nF; C_0805_2012Metric
C8, C10: 1 uF; C_0805_2012Metric
D1: LED; D_0805_2012Metric
FB1: Ferrite_Bead_Small; R_0805_2012Metric
H1, H2: MountingHole; MountingHole_2.2mm_M2
J1: Conn_01x06_Male; PinSocket_1x06_P2.54mm_Vertical
J2: RJ45; RJ45_kycon_GMX-SMT2-S-88-TR_Horizontal
R1, R3, R7: 12K; R_0805_2012Metric
R2: 2M2; R_0805_2012Metric
RESET1: RESET; SW_SPST_TL3342
U1: STM32L041K6Tx; LQFP-32_7x7mm_P0.8mm
U3: SoilSonde; soilSonde
Y1: 32KHz; Crystal_SMD_3215-2Pin_3.2x1.5mm

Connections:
+3V3: BOOT1.1, C5.1, C6.1, C10.1, FB1.2, J1.1, J2.1, U1.1, U1.17
GND: C1.2, C2.2, C4.2, C5.2, C6.2, C7.1, C8.1, C10.2, D1.1, J1.6, J2.8, R7.2, RESET1.1, U1.16, U1.32, U3.1
MISO: J2.4, U1.12
MOSI: J2.5, U1.13
NSS: J2.2, U1.10
unnamed: BOOT1.2, R7.1, U1.31
unnamed: C1.1, U1.3, Y1.1
unnamed: C2.1, U1.2, Y1.2
unnamed: C4.1, RESET1.2, U1.4
unnamed: D1.2, R3.2
unnamed: R1.1, U1.25
unnamed: R2.2, U1.26
unnamed: R3.1, U1.18
RX: J1.2, U1.9
SCK: J2.3, U1.11
SONDE: R1.2, R2.1, U3.2
SWCLK: J1.4, J2.6, U1.24
SWDIO: J1.5, J2.7, U1.23
TX: J1.3, U1.8
VDDA: C7.2, C8.2, FB1.1, U1.5
